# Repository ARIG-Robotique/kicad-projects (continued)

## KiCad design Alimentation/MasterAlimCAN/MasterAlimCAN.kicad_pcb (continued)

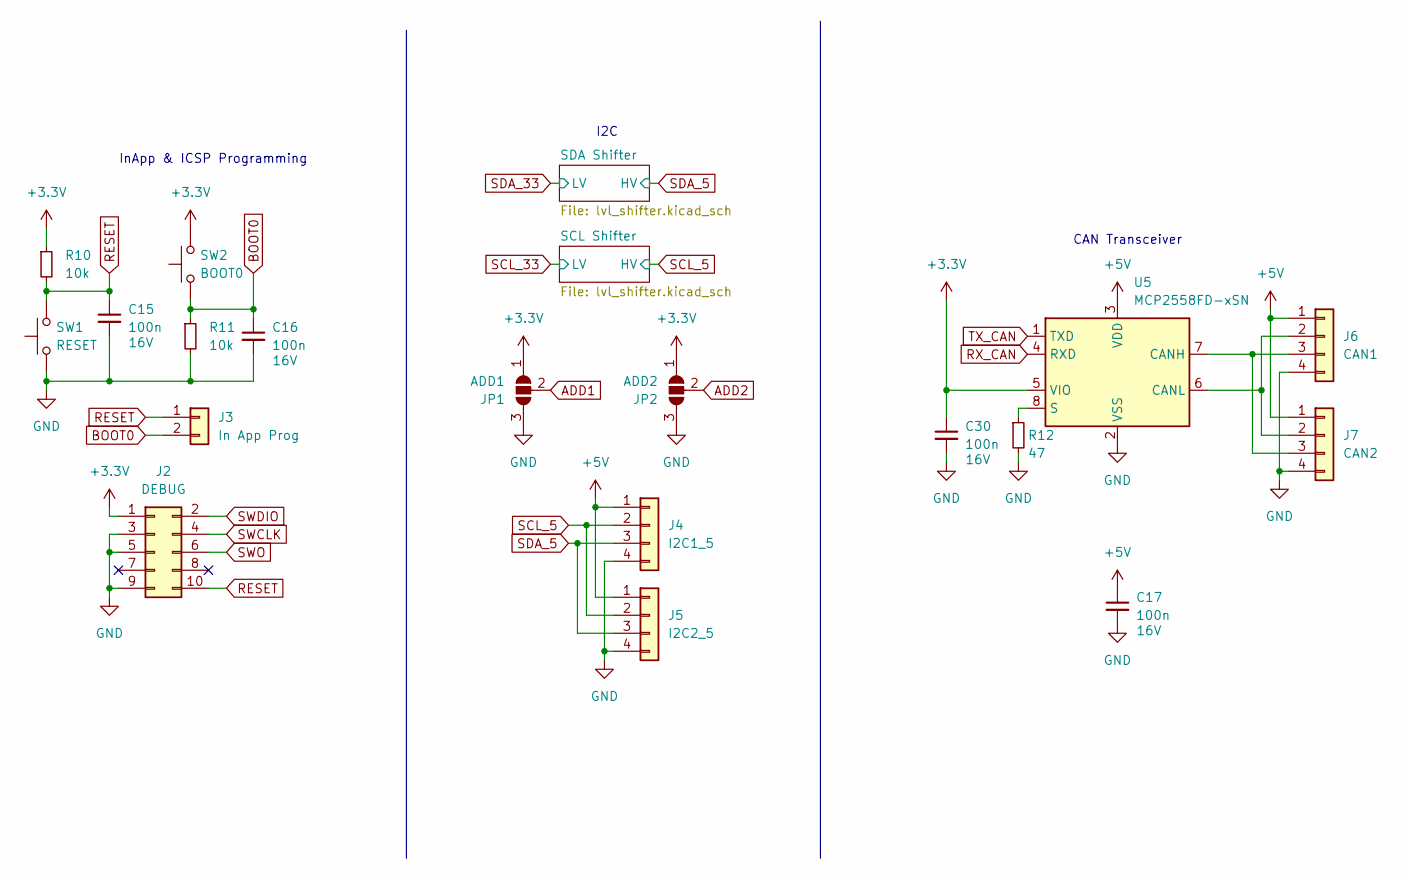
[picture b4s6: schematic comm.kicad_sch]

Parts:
C15, C16, C17, C30: 100n; C_0402_1005Metric_Pad0.74x0.62mm_HandSolder; LCSC Part C1525
J2: DEBUG; PinHeader_2x05_P1.27mm_Vertical_SMD; LCSC Part C5160761
J3: In App Prog; JST_PH_S2B-PH-K_1x02_P2.00mm_Horizontal; JLCPCB BOM 0
J4: I2C1_5; JST_PH_S4B-PH-K_1x04_P2.00mm_Horizontal; JLCPCB BOM 0
J5: I2C2_5; JST_PH_S4B-PH-K_1x04_P2.00mm_Horizontal; JLCPCB BOM 0
J6: CAN1; JST_PH_S4B-PH-K_1x04_P2.00mm_Horizontal; JLCPCB BOM 0
J7: CAN2; JST_PH_S4B-PH-K_1x04_P2.00mm_Horizontal; JLCPCB BOM 0
JP1: ADD1; SolderJumper-3_P1.3mm_Open_RoundedPad1.0x1.5mm; JLCPCB BOM 0
JP2: ADD2; SolderJumper-3_P1.3mm_Open_RoundedPad1.0x1.5mm; JLCPCB BOM 0
R10, R11: 10k; R_0805_2012Metric_Pad1.20x1.40mm_HandSolder; LCSC Part C17414
R12: 47; R_0402_1005Metric_Pad0.72x0.64mm_HandSolder; LCSC Part C25118
SW1: RESET; SW_TS_1088_AR_3x4x2; LCSC Part C720477
SW2: BOOT0; SW_TS_1088_AR_3x4x2; LCSC Part C720477
U5: MCP2558FD-xSN; SOIC-8_3.9x4.9mm_P1.27mm; LCSC Part C124015

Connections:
+3.3V: C30.1, J2.1, JP1.1 (A), JP2.1 (A), R10.1, SW2.2, U5.5 (VIO); also elsewhere on the board
+5V: C17.1, J4.1, J5.1, J6.1, J7.1, U5.3 (VDD); also elsewhere on the board
ADD1: JP1.2 (C); also elsewhere on the board
ADD2: JP2.2 (C); also elsewhere on the board
BOOT0: C16.1, J3.2, R11.1, SW2.1; also elsewhere on the board
GND: C15.2, C16.2, C17.2, C30.2, J2.3, J2.5, J2.9, J4.4, J5.4, J6.4, J7.4, JP1.3 (B), JP2.3 (B), R11.2, R12.2, SW1.1, U5.2 (VSS); also elsewhere on the board
unnamed: J6.2, J7.2, U5.6 (CANL)
unnamed: J6.3, J7.3, U5.7 (CANH)
unnamed: R12.1, U5.8 (S)
RESET: C15.1, J2.10, J3.1, R10.2, SW1.2; also elsewhere on the board
RX_CAN: U5.4 (RXD); also elsewhere on the board
SCL_5: J4.2, J5.2; also elsewhere on the board
SDA_5: J4.3, J5.3; also elsewhere on the board
SWCLK: J2.4; also elsewhere on the board
SWDIO: J2.2; also elsewhere on the board
SWO: J2.6; also elsewhere on the board
TX_CAN: U5.1 (TXD); also elsewhere on the board

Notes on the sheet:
CAN Transceiver
I2C
InApp & ICSP Programming

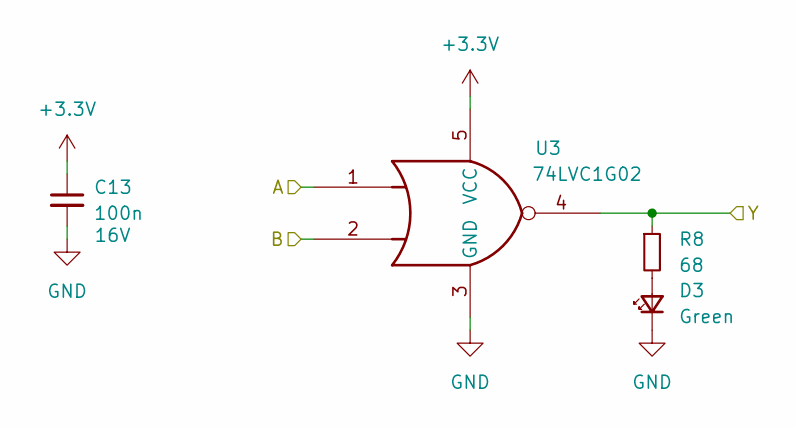
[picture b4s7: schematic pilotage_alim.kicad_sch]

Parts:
C13: 100n; C_0402_1005Metric_Pad0.74x0.62mm_HandSolder; LCSC Part C1525
D3: Green; LED_0805_2012Metric_Pad1.15x1.40mm_HandSolder; LCSC Part C63855
R8: 68; R_0805_2012Metric_Pad1.20x1.40mm_HandSolder; LCSC Part C17802
U3: 74LVC1G02; SOT-23-5_HandSoldering; LCSC Part C16360

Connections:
+3.3V: C13.1, U3.5 (VCC); also elsewhere on the board
AU: U3.1; also elsewhere on the board
EN_ALIM_2: R8.1, U3.4; also elsewhere on the board
GND: C13.2, D3.1 (K), U3.3 (GND); also elsewhere on the board
unnamed: D3.2 (A), R8.2
PIL_ALIM_2: U3.2; also elsewhere on the board

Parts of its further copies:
C14: 100n; C_0402_1005Metric_Pad0.74x0.62mm_HandSolder; LCSC Part C1525
D4: Green; LED_0805_2012Metric_Pad1.15x1.40mm_HandSolder; LCSC Part C63855
R9: 68; R_0805_2012Metric_Pad1.20x1.40mm_HandSolder; LCSC Part C17802
U4: 74LVC1G02; SOT-23-5_HandSoldering; LCSC Part C16360

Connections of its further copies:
+3.3V: C14.1, U4.5 (VCC); also elsewhere on the board
AU: U4.1; also elsewhere on the board
EN_ALIM_3: R9.1, U4.4; also elsewhere on the board
GND: C14.2, D4.1 (K), U4.3 (GND); also elsewhere on the board
unnamed: D4.2 (A), R9.2
PIL_ALIM_3: U4.2; also elsewhere on the board

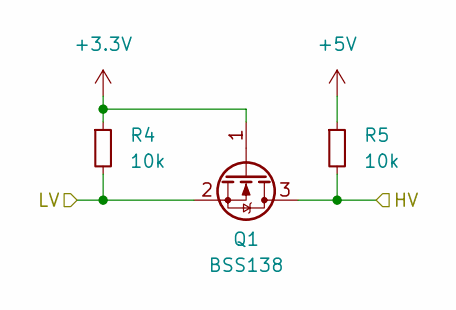
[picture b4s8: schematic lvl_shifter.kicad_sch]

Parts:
Q1: BSS138; SOT-23; LCSC Part C426569
R4, R5: 10k; R_0805_2012Metric_Pad1.20x1.40mm_HandSolder; LCSC Part C17414

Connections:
+3.3V: Q1.1 (G), R4.1; also elsewhere on the board
+5V: R5.1; also elsewhere on the board
SDA_5: Q1.3 (D), R5.2; also elsewhere on the board
SDA_33: Q1.2 (S), R4.2; also elsewhere on the board

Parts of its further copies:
Q2: BSS138; SOT-23; LCSC Part C426569
R6, R7: 10k; R_0805_2012Metric_Pad1.20x1.40mm_HandSolder; LCSC Part C17414

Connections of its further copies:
+3.3V: Q2.1 (G), R6.1; also elsewhere on the board
+5V: R7.1; also elsewhere on the board
SCL_5: Q2.3 (D), R7.2; also elsewhere on the board
SCL_33: Q2.2 (S), R6.2; also elsewhere on the board

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
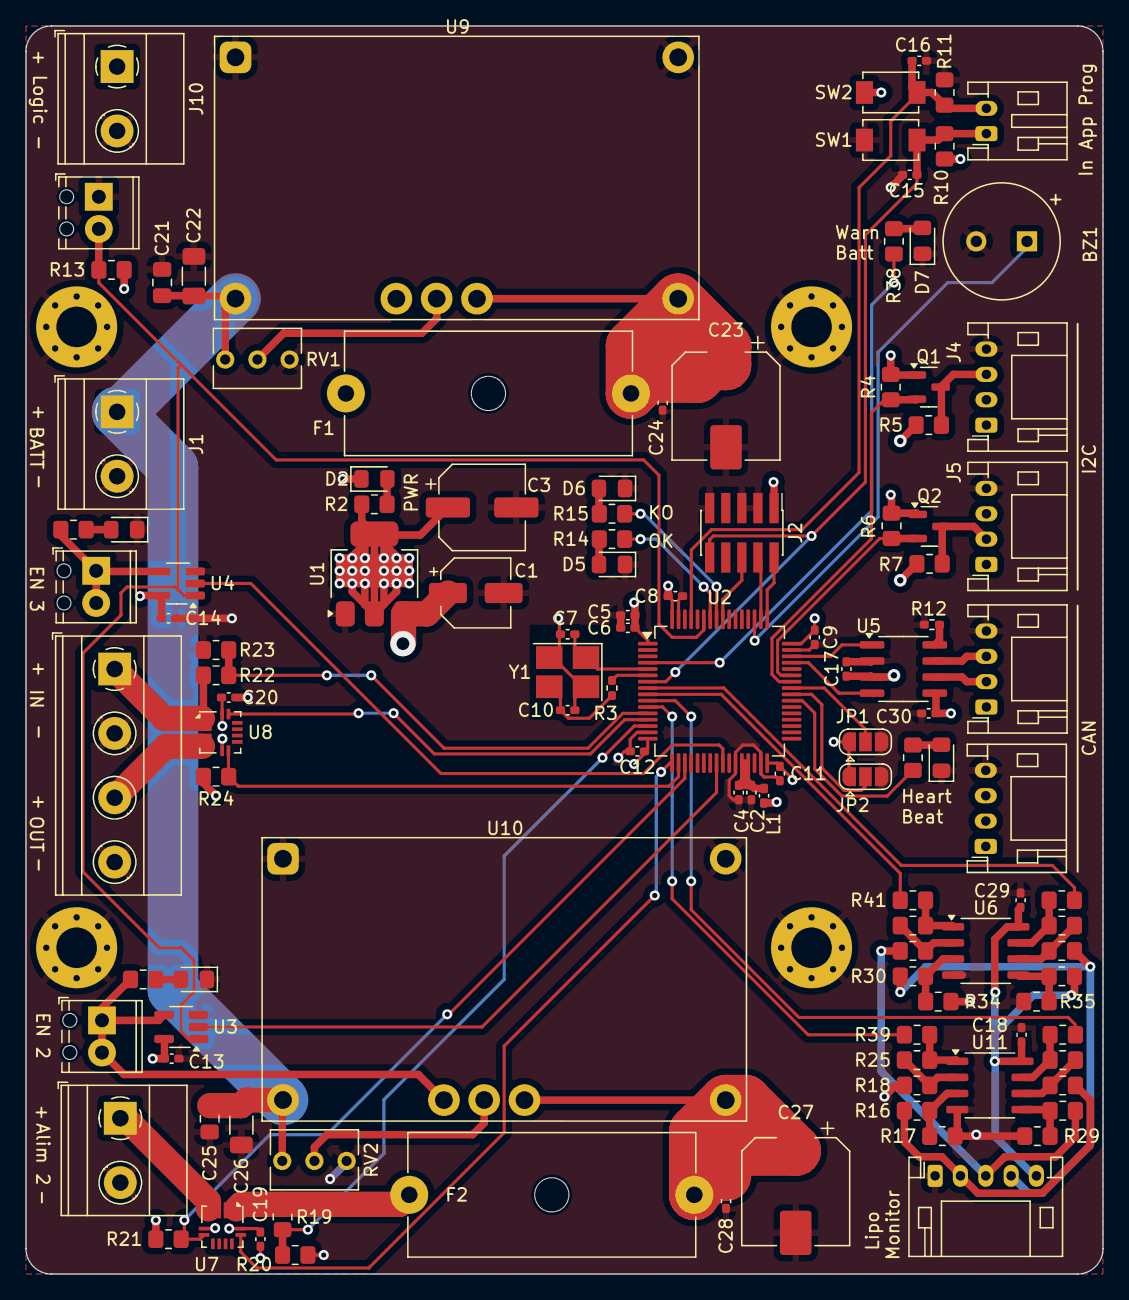
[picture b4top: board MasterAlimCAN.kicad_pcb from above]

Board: 4 copper layers, 85.0 x 98.5 mm, 121 parts (0 on the bottom side), 75 nets.

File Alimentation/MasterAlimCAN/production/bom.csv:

Designator,Footprint,Quantity,Value,LCSC Part #
BZ1,MagneticBuzzer_CUI_CST-931RP-A,1,Buzzer,
C1,CP_Elec_5x5.3,1,100u,C249463
"C10, C7",0402,2,12p,C1547
"C11, C12, C13, C14, C15, C16, C17, C19, C20, C30, C6, C8, C9",0402,13,100n,C1525
"C18, C29",0402,2,100n,C100072
"C2, C24, C28",0402,3,1u,C52923
"C21, C25",0805,2,1u,C28323
"C22, C26",1206,2,2.2u,C50254
"C23, C27",CP_Elec_8x10,2,330u,C134842
C3,CP_Elec_6.3x7.7,1,330u,C249900
C4,0402,1,10n,C15195
C5,0402,1,4.7u,C23733
"D1, D2, D3, D4, D5",0805,5,Green,C63855
"D6, D7",0805,2,Red,C72037
"F1, F2",Fuseholder_Cylinder-5x20mm_Schurter_0031_8201_Horizontal_Open,2,6A,
"H1, H2, H3, H4",MountingHole_3.2mm_M3_Pad_Via,4,MountingHole_Pad,
J1,"TerminalBlock_Phoenix_MKDS-1,5-2-5.08_1x02_P5.08mm_Horizontal",1,BATT,
J10,"TerminalBlock_Phoenix_MKDS-1,5-2-5.08_1x02_P5.08mm_Horizontal",1,Alim Log,
J11,"TerminalBlock_Phoenix_MKDS-1,5-2-5.08_1x02_P5.08mm_Horizontal",1,Alim 2,
J12,"TerminalBlock_Phoenix_MPT-0,5-2-2.54_1x02_P2.54mm_Horizontal",1,EN 3,
J13,"TerminalBlock_Phoenix_MKDS-1,5-4-5.08_1x04_P5.08mm_Horizontal",1,Alim 3,
J15,JST_PH_S5B-PH-K_1x05_P2.00mm_Horizontal,1,Lipo Cells,
J2,PinHeader_2x05_P1.27mm_Vertical_SMD,1,DEBUG,C5160761
J3,JST_PH_S2B-PH-K_1x02_P2.00mm_Horizontal,1,In App Prog,
J4,JST_PH_S4B-PH-K_1x04_P2.00mm_Horizontal,1,I2C1_5,
J5,JST_PH_S4B-PH-K_1x04_P2.00mm_Horizontal,1,I2C2_5,
J6,JST_PH_S4B-PH-K_1x04_P2.00mm_Horizontal,1,CAN1,
J7,JST_PH_S4B-PH-K_1x04_P2.00mm_Horizontal,1,CAN2,
J8,"TerminalBlock_Phoenix_MPT-0,5-2-2.54_1x02_P2.54mm_Horizontal",1,Conn AU,
J9,"TerminalBlock_Phoenix_MPT-0,5-2-2.54_1x02_P2.54mm_Horizontal",1,EN 2,
L1,0402,1,39n,C26443
"Q1, Q2",SOT-23,2,BSS138,C426569
"R1, R14, R15, R2, R38, R8, R9",0805,7,68,C17802
"R10, R11, R13, R16, R18, R21, R24, R26, R27, R30, R31, R32, R33, R4, R5, R6, R7",0805,17,10k,C17414
"R12, R3",0402,2,47,C25118
"R17, R25, R28, R29, R34, R35, R36, R37",0805,8,7.5k,C17807
"R19, R22",0805,2,5.6k,C26024
"R20, R23",0805,2,1.8k,C17398
"R39, R40, R41, R42",0805,4,100k,C25611
SW1,SW_TS_1088_AR_3x4x2,1,RESET,C720477
SW2,SW_TS_1088_AR_3x4x2,1,BOOT0,C720477
U1,SOT-223-3_TabPin2,1,AMS1117-3.3,C6186
"U10, U9",Texas_EUK_R-PDSS-T7_THT,2,PTN78020W_EUK-7,C5219636
"U11, U6",SO-8_3.9x4.9mm_P1.27mm,2,LM358,C9418
U2,LQFP-64_10x10mm_P0.5mm,1,STM32G474RETx,C521608
"U3, U4",SOT-23-5_HandSoldering,2,74LVC1G02,C16360
U5,SOIC-8_3.9x4.9mm_P1.27mm,1,MCP2558FD-xSN,C124015
"U7, U8",Allegro_QFN-12-10-1EP_3x3mm_P0.5mm,2,ACS711xEXLT-15AB,C150824
Y1,Crystal_SMD_3225-4Pin_3.2x2.5mm_HandSoldering,1,16MHz,C13738

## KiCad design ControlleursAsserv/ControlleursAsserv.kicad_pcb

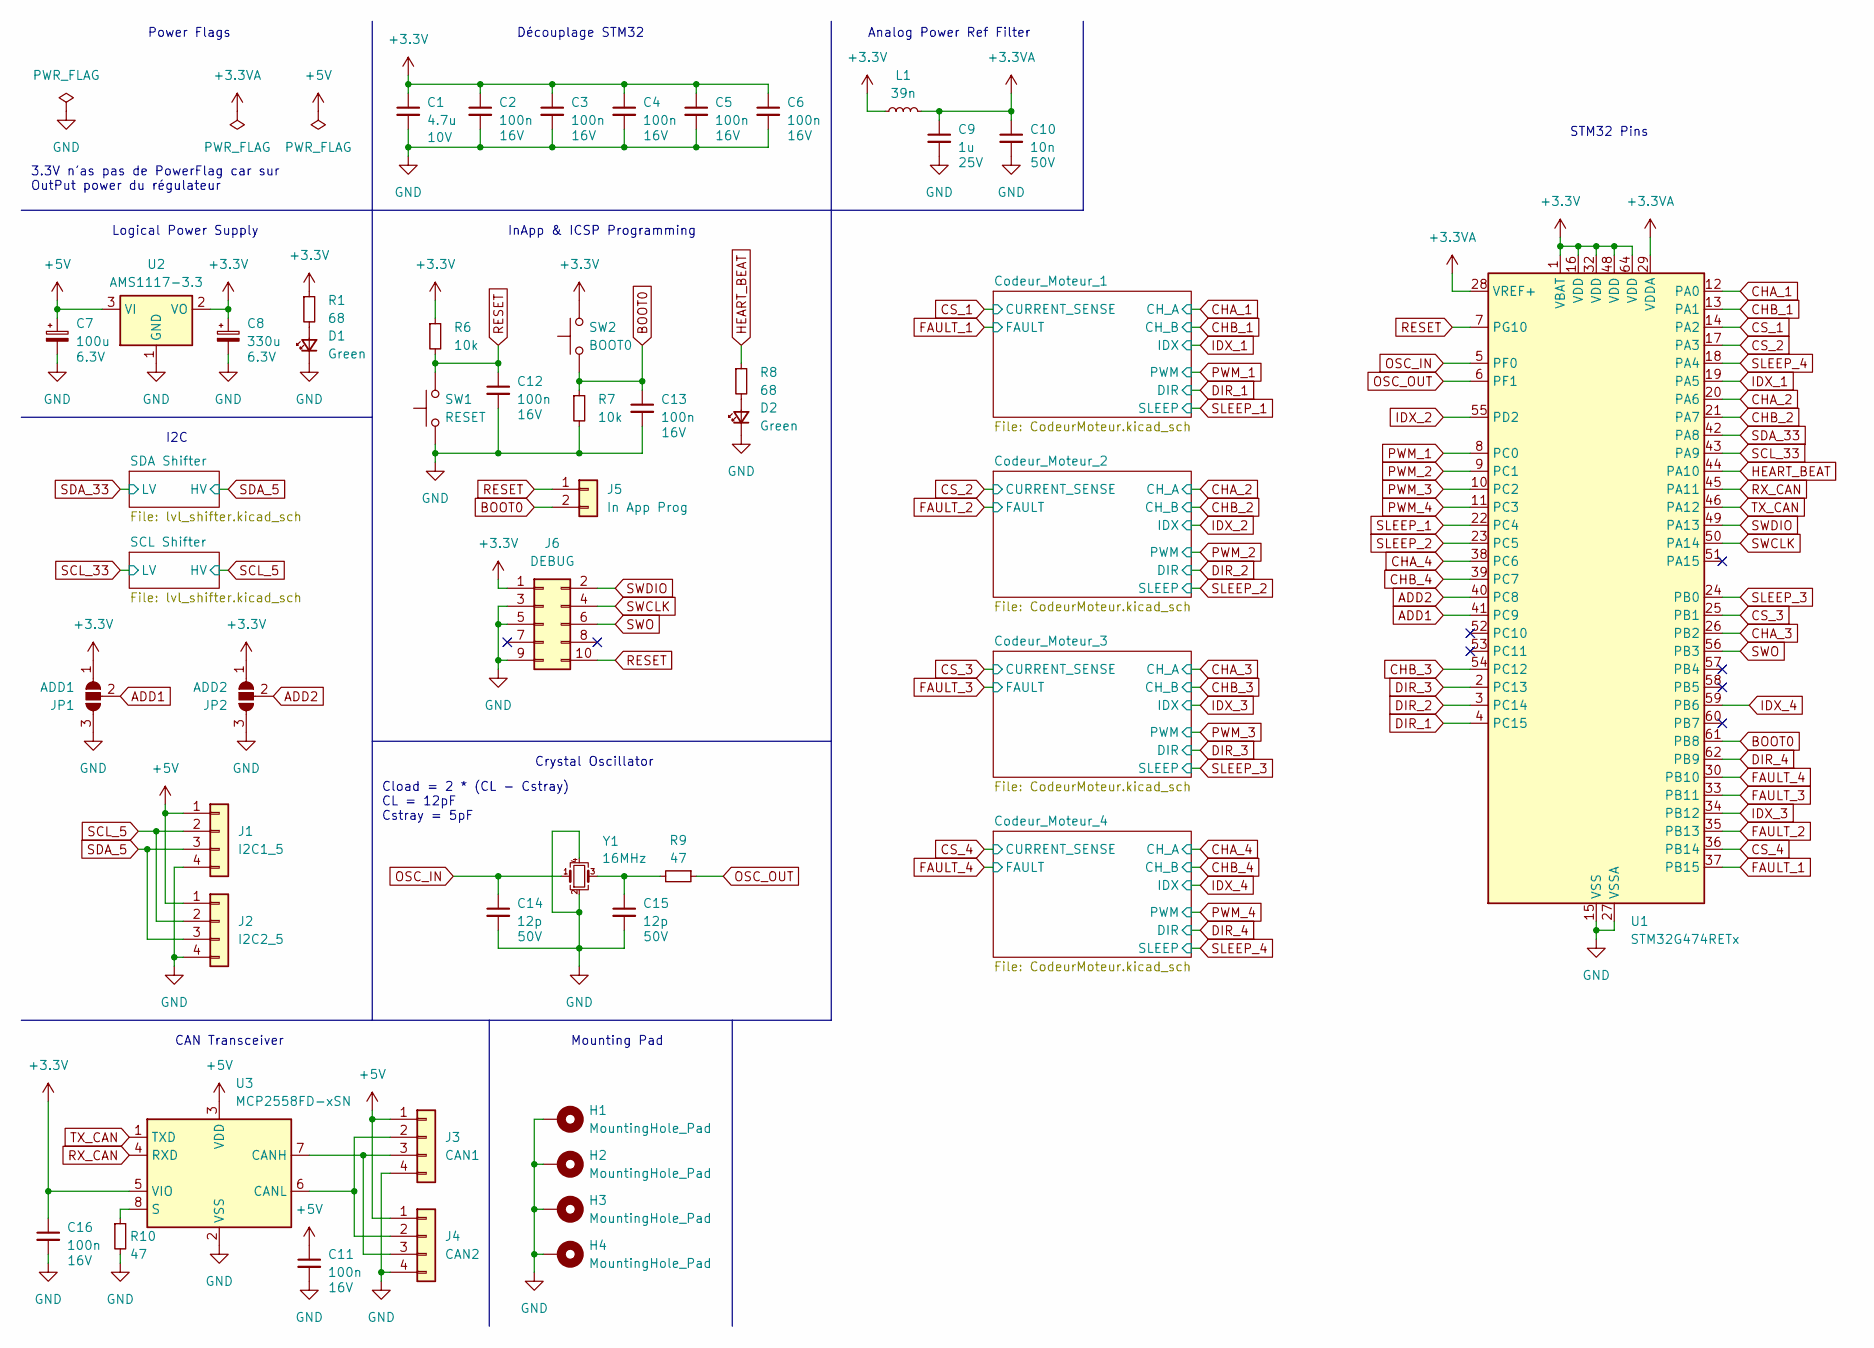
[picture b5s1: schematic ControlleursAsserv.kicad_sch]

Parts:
C1: 4.7u; C_0402_1005Metric_Pad0.74x0.62mm_HandSolder; LCSC Part C23733
C2, C3, C4, C5, C6, C11, C12, C13, C16: 100n; C_0402_1005Metric_Pad0.74x0.62mm_HandSolder; LCSC Part C1525
C7: 100u; CP_Elec_5x5.3; LCSC Part C249463
C8: 330u; CP_Elec_6.3x7.7; LCSC Part C249900
C9: 1u; C_0402_1005Metric_Pad0.74x0.62mm_HandSolder; LCSC Part C52923
C10: 10n; C_0402_1005Metric_Pad0.74x0.62mm_HandSolder; LCSC Part C15195
C14, C15: 12p; C_0402_1005Metric_Pad0.74x0.62mm_HandSolder; LCSC Part C1547
D1, D2: Green; LED_0805_2012Metric_Pad1.15x1.40mm_HandSolder; LCSC Part C63855
H1, H2, H3, H4: MountingHole_Pad; MountingHole_3.2mm_M3_Pad_Via; JLCPCB BOM 0
J1: I2C1_5; JST_PH_S4B-PH-K_1x04_P2.00mm_Horizontal; JLCPCB BOM 0
J2: I2C2_5; JST_PH_S4B-PH-K_1x04_P2.00mm_Horizontal; JLCPCB BOM 0
J3: CAN1; JST_PH_S4B-PH-K_1x04_P2.00mm_Horizontal; JLCPCB BOM 0
J4: CAN2; JST_PH_S4B-PH-K_1x04_P2.00mm_Horizontal; JLCPCB BOM 0
J5: In App Prog; JST_PH_S2B-PH-K_1x02_P2.00mm_Horizontal; JLCPCB BOM 0
J6: DEBUG; PinHeader_2x05_P1.27mm_Vertical_SMD; LCSC Part C5160761
JP1: ADD1; SolderJumper-3_P1.3mm_Open_RoundedPad1.0x1.5mm; JLCPCB BOM 0
JP2: ADD2; SolderJumper-3_P1.3mm_Open_RoundedPad1.0x1.5mm; JLCPCB BOM 0
L1: 39n; L_0402_1005Metric_Pad0.77x0.64mm_HandSolder; LCSC Part C26443
R1, R8: 68; R_0805_2012Metric_Pad1.20x1.40mm_HandSolder; LCSC Part C17802
R6, R7: 10k; R_0805_2012Metric_Pad1.20x1.40mm_HandSolder; LCSC Part C17414
R9, R10: 47; R_0402_1005Metric_Pad0.72x0.64mm_HandSolder; LCSC Part C25118
SW1: RESET; SW_TS_1088_AR_3x4x2; LCSC Part C720477
SW2: BOOT0; SW_TS_1088_AR_3x4x2; LCSC Part C720477
U1: STM32G474RETx; LQFP-64_10x10mm_P0.5mm; LCSC Part C521608
U2: AMS1117-3.3; SOT-223-3_TabPin2; LCSC Part C6186
U3: MCP2558FD-xSN; SOIC-8_3.9x4.9mm_P1.27mm; LCSC Part C124015
Y1: 16MHz; Crystal_SMD_3225-4Pin_3.2x2.5mm_HandSoldering; LCSC Part C13738

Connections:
+3.3V: C1.1, C2.1, C3.1, C4.1, C5.1, C6.1, C8.1, C16.1, J6.1, JP1.1 (A), JP2.1 (A), L1.1, R1.1, R6.1, SW2.2, U1.1 (VBAT), U1.16 (VDD), U1.32 (VDD), U1.48 (VDD), U1.64 (VDD), U2.2 (VO), U3.5 (VIO); also elsewhere on the board
+3.3VA: C9.1, C10.1, L1.2, U1.28 (VREF+), U1.29 (VDDA)
+5V: C7.1, C11.1, J1.1, J2.1, J3.1, J4.1, U2.3 (VI), U3.3 (VDD); also elsewhere on the board
ADD1: JP1.2 (C), U1.41 (PC9)
ADD2: JP2.2 (C), U1.40 (PC8)
BOOT0: C13.1, J5.2, R7.1, SW2.1, U1.61 (PB8)
CHA_1: U1.12 (PA0); also elsewhere on the board
CHA_2: U1.20 (PA6); also elsewhere on the board
CHA_3: U1.26 (PB2); also elsewhere on the board
CHA_4: U1.38 (PC6); also elsewhere on the board
CHB_1: U1.13 (PA1); also elsewhere on the board
CHB_2: U1.21 (PA7); also elsewhere on the board
CHB_3: U1.54 (PC12); also elsewhere on the board
CHB_4: U1.39 (PC7); also elsewhere on the board
CS_1: U1.14 (PA2); also elsewhere on the board
CS_2: U1.17 (PA3); also elsewhere on the board
CS_3: U1.25 (PB1); also elsewhere on the board
CS_4: U1.36 (PB14); also elsewhere on the board
DIR_1: U1.4 (PC15); also elsewhere on the board
DIR_2: U1.3 (PC14); also elsewhere on the board
DIR_3: U1.2 (PC13); also elsewhere on the board
DIR_4: U1.62 (PB9); also elsewhere on the board
FAULT_1: U1.37 (PB15); also elsewhere on the board
FAULT_2: U1.35 (PB13); also elsewhere on the board
FAULT_3: U1.33 (PB11); also elsewhere on the board
FAULT_4: U1.30 (PB10); also elsewhere on the board
GND: C1.2, C2.2, C3.2, C4.2, C5.2, C6.2, C7.2, C8.2, C9.2, C10.2, C11.2, C12.2, C13.2, C14.2, C15.2, C16.2, D1.1 (K), D2.1 (K), H1.1, H2.1, H3.1, H4.1, J1.4, J2.4, J3.4, J4.4, J6.3, J6.5, J6.9, JP1.3 (B), JP2.3 (B), R7.2, R10.2, SW1.1, U1.15 (VSS), U1.27 (VSSA), U1.31 (VSS), U1.47 (VSS), U1.63 (VSS), U2.1 (GND), U3.2 (VSS), Y1.2, Y1.4; also elsewhere on the board
HEART_BEAT: R8.1, U1.44 (PA10)
IDX_1: U1.19 (PA5); also elsewhere on the board
IDX_2: U1.55 (PD2); also elsewhere on the board
IDX_3: U1.34 (PB12); also elsewhere on the board
IDX_4: U1.59 (PB6); also elsewhere on the board
unnamed: C15.1, R9.2, Y1.3
unnamed: D1.2 (A), R1.2
unnamed: D2.2 (A), R8.2
unnamed: J3.2, J4.2, U3.6 (CANL)
unnamed: J3.3, J4.3, U3.7 (CANH)
unnamed: R10.1, U3.8 (S)
OSC_IN: C14.1, U1.5 (PF0), Y1.1
OSC_OUT: R9.1, U1.6 (PF1)
PWM_1: U1.8 (PC0); also elsewhere on the board
PWM_2: U1.9 (PC1); also elsewhere on the board
PWM_3: U1.10 (PC2); also elsewhere on the board
PWM_4: U1.11 (PC3); also elsewhere on the board
RESET: C12.1, J5.1, J6.10, R6.2, SW1.2, U1.7 (PG10)
RX_CAN: U1.45 (PA11), U3.4 (RXD)
SCL_5: J1.2, J2.2; also elsewhere on the board
SCL_33: U1.43 (PA9); also elsewhere on the board
SDA_5: J1.3, J2.3; also elsewhere on the board
SDA_33: U1.42 (PA8); also elsewhere on the board
SLEEP_1: U1.22 (PC4); also elsewhere on the board
SLEEP_2: U1.23 (PC5); also elsewhere on the board
SLEEP_3: U1.24 (PB0); also elsewhere on the board
SLEEP_4: U1.18 (PA4); also elsewhere on the board
SWCLK: J6.4, U1.50 (PA14)
SWDIO: J6.2, U1.49 (PA13)
SWO: J6.6, U1.56 (PB3)
TX_CAN: U1.46 (PA12), U3.1 (TXD)

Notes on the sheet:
I2C
Analog Power Ref Filter
STM32 Pins
Mounting Pad
Crystal Oscillator
3.3V n'as pas de PowerFlag car sur OutPut power du régulateur
Découplage STM32
Power Flags
CAN Transceiver
InApp & ICSP Programming
Logical Power Supply
Cload = 2 * (CL - Cstray) CL = 12pF Cstray = 5pF

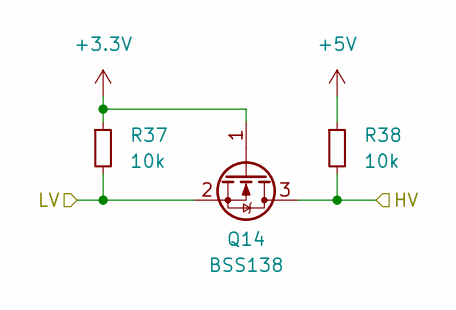
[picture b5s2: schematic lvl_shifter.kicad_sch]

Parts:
Q14: BSS138; SOT-23; LCSC Part C426569
R37, R38: 10k; R_0805_2012Metric_Pad1.20x1.40mm_HandSolder; LCSC Part C17414

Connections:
+3.3V: Q14.1 (G), R37.1; also elsewhere on the board
+5V: R38.1; also elsewhere on the board
SDA_5: Q14.3 (D), R38.2; also elsewhere on the board
SDA_33: Q14.2 (S), R37.2; also elsewhere on the board

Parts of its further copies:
Q1, Q2, Q3, Q4, Q5, Q6, Q7, Q8, Q9, Q10, Q11, Q12, Q13: BSS138; SOT-23; LCSC Part C426569
R2, R3, R4, R5, R11, R12, R13, R14, R17, R18, R19, R20, R21, R22, R24, R25, R26, R27, R28, R29, R31, R32, R33, R34, R35, R36: 10k; R_0805_2012Metric_Pad1.20x1.40mm_HandSolder; LCSC Part C17414

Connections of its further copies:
+3.3V: Q1.1 (G), Q2.1 (G), Q3.1 (G), Q4.1 (G), Q5.1 (G), Q6.1 (G), Q7.1 (G), Q8.1 (G), Q9.1 (G), Q10.1 (G), Q11.1 (G), Q12.1 (G), Q13.1 (G), R2.1, R4.1, R11.1, R13.1, R17.1, R19.1, R21.1, R24.1, R26.1, R28.1, R31.1, R33.1, R35.1; also elsewhere on the board
+5V: R3.1, R5.1, R12.1, R14.1, R18.1, R20.1, R22.1, R25.1, R27.1, R29.1, R32.1, R34.1, R36.1; also elsewhere on the board
/Codeur_Moteur_1/CHA Shifter/HV: Q1.3 (D), R3.2; also elsewhere on the board
/Codeur_Moteur_1/CHB Shifter/HV: Q3.3 (D), R12.2; also elsewhere on the board
/Codeur_Moteur_1/IDX Shifter/HV: Q4.3 (D), R14.2; also elsewhere on the board
/Codeur_Moteur_2/CHA Shifter/HV: Q5.3 (D), R18.2; also elsewhere on the board
/Codeur_Moteur_2/CHB Shifter/HV: Q6.3 (D), R20.2; also elsewhere on the board
/Codeur_Moteur_2/IDX Shifter/HV: Q7.3 (D), R22.2; also elsewhere on the board
/Codeur_Moteur_3/CHA Shifter/HV: Q10.3 (D), R29.2; also elsewhere on the board
/Codeur_Moteur_3/CHB Shifter/HV: Q8.3 (D), R25.2; also elsewhere on the board
/Codeur_Moteur_3/IDX Shifter/HV: Q9.3 (D), R27.2; also elsewhere on the board
/Codeur_Moteur_4/CHA Shifter/HV: Q12.3 (D), R34.2; also elsewhere on the board
/Codeur_Moteur_4/CHB Shifter/HV: Q13.3 (D), R36.2; also elsewhere on the board
/Codeur_Moteur_4/IDX Shifter/HV: Q11.3 (D), R32.2; also elsewhere on the board
CHA_1: Q1.2 (S), R2.2; also elsewhere on the board
CHA_2: Q5.2 (S), R17.2; also elsewhere on the board
CHA_3: Q10.2 (S), R28.2; also elsewhere on the board
CHA_4: Q12.2 (S), R33.2; also elsewhere on the board
CHB_1: Q3.2 (S), R11.2; also elsewhere on the board
CHB_2: Q6.2 (S), R19.2; also elsewhere on the board
CHB_3: Q8.2 (S), R24.2; also elsewhere on the board
CHB_4: Q13.2 (S), R35.2; also elsewhere on the board
IDX_1: Q4.2 (S), R13.2; also elsewhere on the board
IDX_2: Q7.2 (S), R21.2; also elsewhere on the board
IDX_3: Q9.2 (S), R26.2; also elsewhere on the board
IDX_4: Q11.2 (S), R31.2; also elsewhere on the board
SCL_5: Q2.3 (D), R5.2; also elsewhere on the board
SCL_33: Q2.2 (S), R4.2; also elsewhere on the board

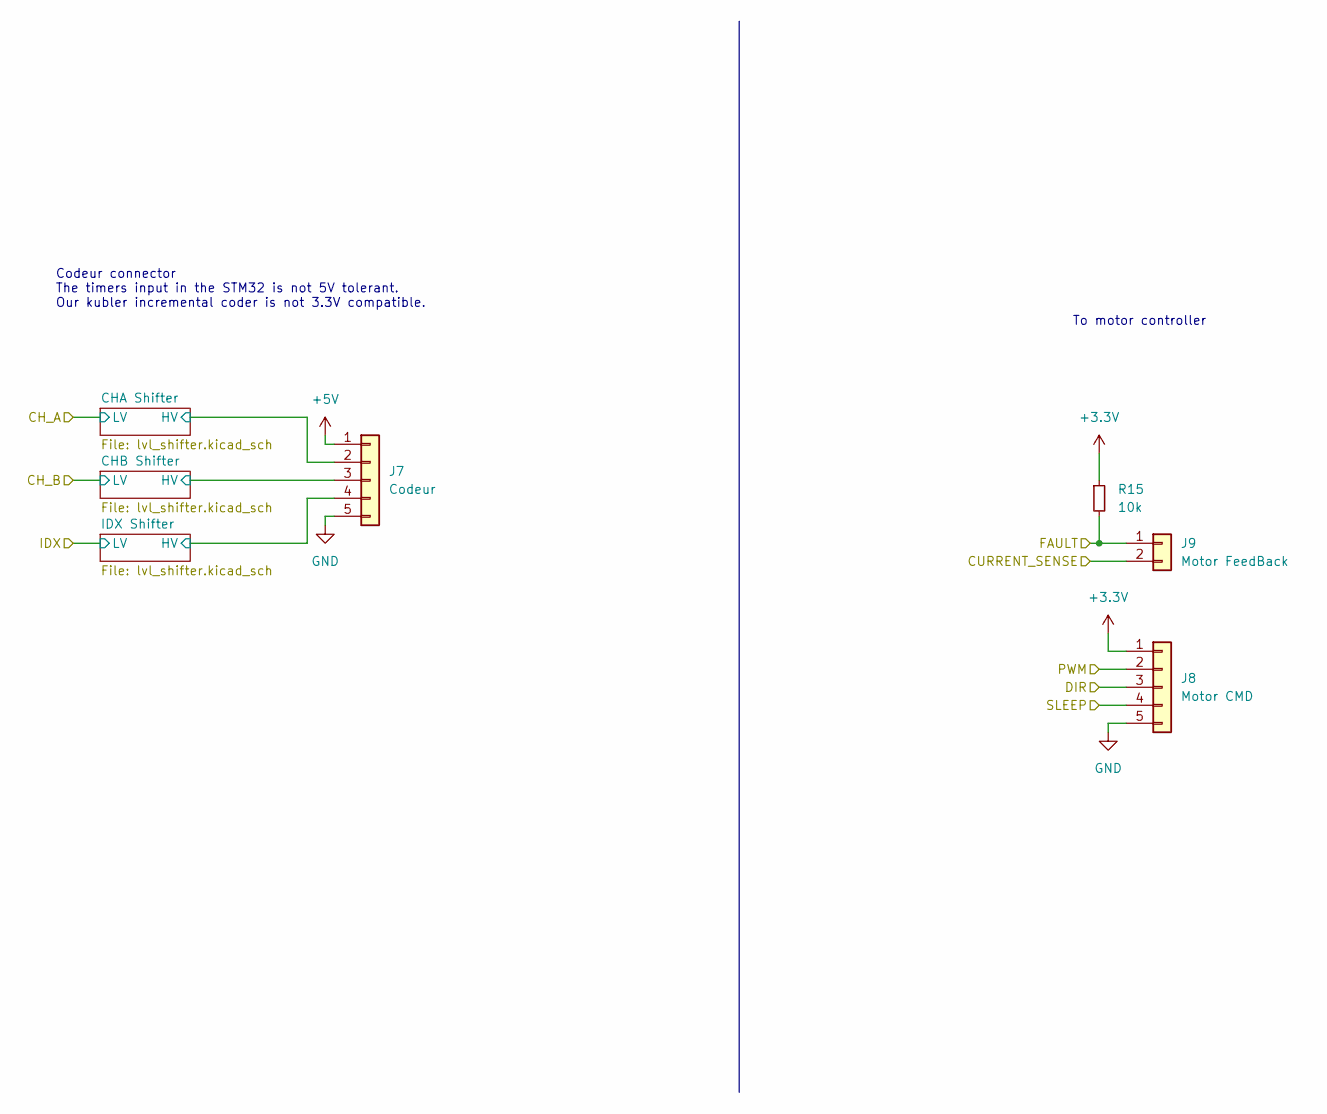
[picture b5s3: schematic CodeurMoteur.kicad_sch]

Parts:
J7: Codeur; JST_PH_S5B-PH-K_1x05_P2.00mm_Horizontal; JLCPCB BOM 0
J8: Motor CMD; JST_PH_S5B-PH-K_1x05_P2.00mm_Horizontal; JLCPCB BOM 0
J9: Motor FeedBack; JST_PH_S2B-PH-K_1x02_P2.00mm_Horizontal; JLCPCB BOM 0
R15: 10k; R_0805_2012Metric_Pad1.20x1.40mm_HandSolder; LCSC Part C17414

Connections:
+3.3V: J8.1, R15.1; also elsewhere on the board
+5V: J7.1; also elsewhere on the board
/Codeur_Moteur_1/CHA Shifter/HV: J7.2; also elsewhere on the board
/Codeur_Moteur_1/CHB Shifter/HV: J7.3; also elsewhere on the board
/Codeur_Moteur_1/IDX Shifter/HV: J7.4; also elsewhere on the board
CS_1: J9.2; also elsewhere on the board
DIR_1: J8.3; also elsewhere on the board
FAULT_1: J9.1, R15.2; also elsewhere on the board
GND: J7.5, J8.5; also elsewhere on the board
PWM_1: J8.2; also elsewhere on the board
SLEEP_1: J8.4; also elsewhere on the board

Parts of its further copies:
J10, J13, J16: Codeur; JST_PH_S5B-PH-K_1x05_P2.00mm_Horizontal; JLCPCB BOM 0
J11, J14, J17: Motor FeedBack; JST_PH_S2B-PH-K_1x02_P2.00mm_Horizontal; JLCPCB BOM 0
J12, J15, J18: Motor CMD; JST_PH_S5B-PH-K_1x05_P2.00mm_Horizontal; JLCPCB BOM 0
R16, R23, R30: 10k; R_0805_2012Metric_Pad1.20x1.40mm_HandSolder; LCSC Part C17414

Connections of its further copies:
+3.3V: J12.1, J15.1, J18.1, R16.1, R23.1, R30.1; also elsewhere on the board
+5V: J10.1, J13.1, J16.1; also elsewhere on the board
/Codeur_Moteur_2/CHA Shifter/HV: J10.2; also elsewhere on the board
/Codeur_Moteur_2/CHB Shifter/HV: J10.3; also elsewhere on the board
/Codeur_Moteur_2/IDX Shifter/HV: J10.4; also elsewhere on the board
/Codeur_Moteur_3/CHA Shifter/HV: J13.2; also elsewhere on the board
/Codeur_Moteur_3/CHB Shifter/HV: J13.3; also elsewhere on the board
/Codeur_Moteur_3/IDX Shifter/HV: J13.4; also elsewhere on the board
/Codeur_Moteur_4/CHA Shifter/HV: J16.2; also elsewhere on the board
/Codeur_Moteur_4/CHB Shifter/HV: J16.3; also elsewhere on the board
/Codeur_Moteur_4/IDX Shifter/HV: J16.4; also elsewhere on the board
CS_2: J11.2; also elsewhere on the board
CS_3: J14.2; also elsewhere on the board
CS_4: J17.2; also elsewhere on the board
DIR_2: J12.3; also elsewhere on the board
DIR_3: J15.3; also elsewhere on the board
DIR_4: J18.3; also elsewhere on the board
FAULT_2: J11.1, R16.2; also elsewhere on the board
FAULT_3: J14.1, R23.2; also elsewhere on the board
FAULT_4: J17.1, R30.2; also elsewhere on the board
GND: J10.5, J12.5, J13.5, J15.5, J16.5, J18.5; also elsewhere on the board
PWM_2: J12.2; also elsewhere on the board
PWM_3: J15.2; also elsewhere on the board
PWM_4: J18.2; also elsewhere on the board
SLEEP_2: J12.4; also elsewhere on the board
SLEEP_3: J15.4; also elsewhere on the board
SLEEP_4: J18.4; also elsewhere on the board

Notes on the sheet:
Codeur connector The timers input in the STM32 is not 5V tolerant. Our kubler incremental coder is not 3.3V compatible.
To motor controller

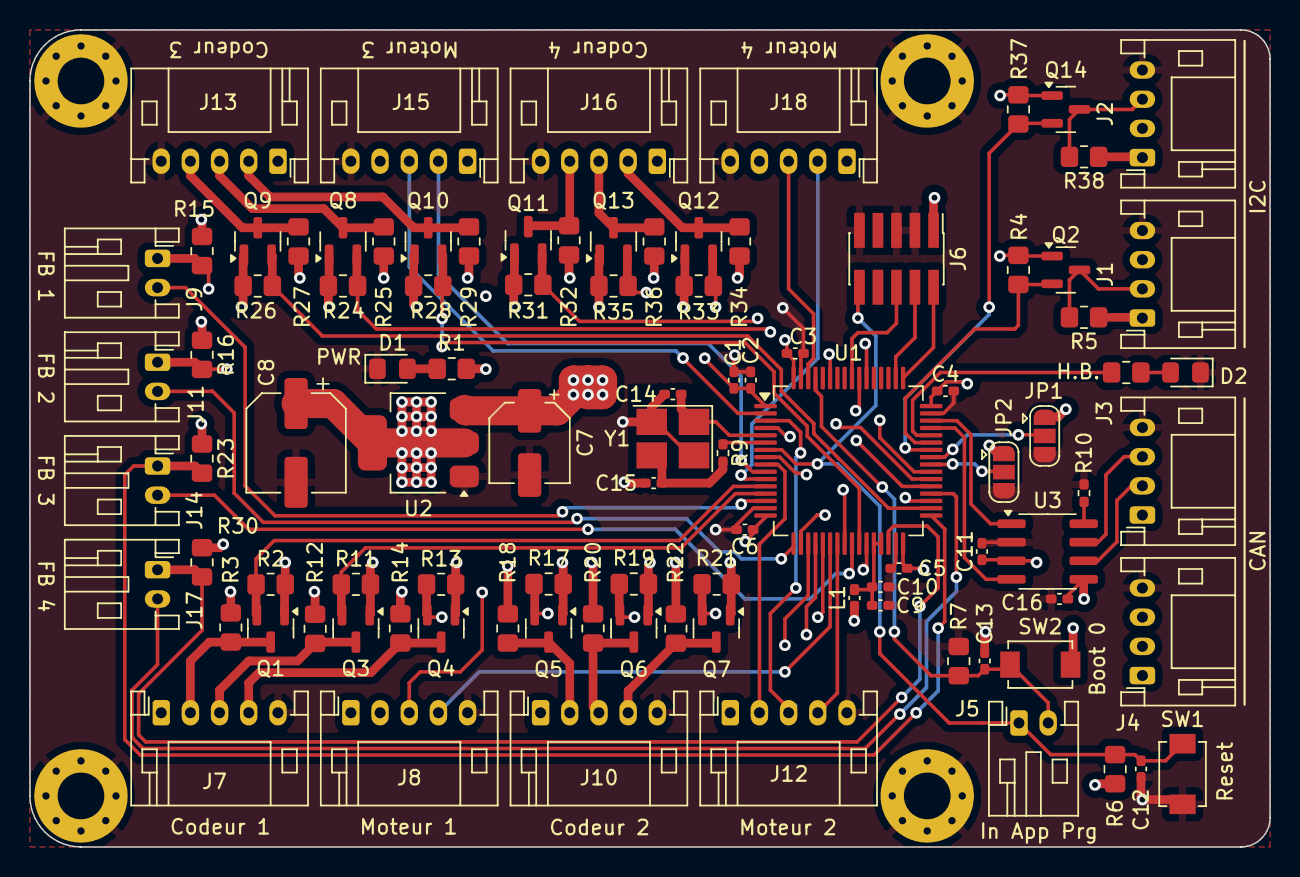
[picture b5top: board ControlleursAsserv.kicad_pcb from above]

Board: 4 copper layers, 85.0 x 56.0 mm, 101 parts (0 on the bottom side), 70 nets.

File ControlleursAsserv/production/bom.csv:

Designator,Footprint,Quantity,Value,LCSC Part #
C1,0402,1,4.7u,C23733
C10,0402,1,10n,C15195
"C11, C12, C13, C16, C2, C3, C4, C5, C6",0402,9,100n,C1525
"C14, C15",0402,2,12p,C1547
C7,CP_Elec_5x5.3,1,100u,C249463
C8,CP_Elec_6.3x7.7,1,330u,C249900
C9,0402,1,1u,C52923
"D1, D2",0805,2,Green,C63855
J1,JST_PH_S4B-PH-K_1x04_P2.00mm_Horizontal,1,I2C1_5,
"J10, J13, J16, J7",JST_PH_S5B-PH-K_1x05_P2.00mm_Horizontal,4,Codeur,
"J11, J14, J17, J9",JST_PH_S2B-PH-K_1x02_P2.00mm_Horizontal,4,Motor FeedBack,
"J12, J15, J18, J8",JST_PH_S5B-PH-K_1x05_P2.00mm_Horizontal,4,Motor CMD,
J2,JST_PH_S4B-PH-K_1x04_P2.00mm_Horizontal,1,I2C2_5,
J3,JST_PH_S4B-PH-K_1x04_P2.00mm_Horizontal,1,CAN1,
J4,JST_PH_S4B-PH-K_1x04_P2.00mm_Horizontal,1,CAN2,
J5,JST_PH_S2B-PH-K_1x02_P2.00mm_Horizontal,1,In App Prog,
J6,PinHeader_2x05_P1.27mm_Vertical_SMD,1,DEBUG,C5160761
L1,0402,1,39n,C26443
"Q1, Q10, Q11, Q12, Q13, Q14, Q2, Q3, Q4, Q5, Q6, Q7, Q8, Q9",SOT-23,14,BSS138,C426569
"R1, R8",0805,2,68,C17802
"R10, R9",0402,2,47,C25118
"R11, R12, R13, R14, R15, R16, R17, R18, R19, R2, R20, R21, R22, R23, R24, R25, R26, R27, R28, R29, R3, R30, R31, R32, R33, R34, R35, R36, R37, R38, R4, R5, R6, R7",0805,34,10k,C17414
SW1,SW_TS_1088_AR_3x4x2,1,RESET,C720477
SW2,SW_TS_1088_AR_3x4x2,1,BOOT0,C720477
U1,LQFP-64_10x10mm_P0.5mm,1,STM32G474RETx,C521608
U2,SOT-223-3_TabPin2,1,AMS1117-3.3,C6186
U3,SOIC-8_3.9x4.9mm_P1.27mm,1,MCP2558FD-xSN,C124015
Y1,Crystal_SMD_3225-4Pin_3.2x2.5mm_HandSoldering,1,16MHz,C13738
